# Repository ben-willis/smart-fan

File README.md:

# Smart Fan Project

A WiFi-enabled smart fan controller built on ESP32-S3 with Home Assistant integration, using ESPHome for firmware management.

## Overview

This project transforms a traditional fan into a smart, connected device with the following capabilities:
- **WiFi Connectivity**: ESP32-S3 microcontroller for wireless control
- **Home Assistant Integration**: Full API integration for home automation
- **Physical Controls**: GPIO-based buttons for manual operation
- **IR Remote Support**: NEC protocol infrared remote control
- **Advanced Features**: 3-speed control, oscillation mode, preset modes (Sleep, Nature, Normal)
- **Custom PCB**: Professionally designed KiCad PCB with production-ready Gerber files

## Documentation

- [Docs Index](docs/README.md)
- [Project Story](docs/project-story.md)
- [UART Protocol](docs/uart-protocol.md)
- [Hardware Notes](docs/hardware-notes.md)

If you are new to this repository, start with [Project Story](docs/project-story.md), then use [UART Protocol](docs/uart-protocol.md) while reviewing firmware behavior.

## Hardware

### Microcontroller
- **Board**: ESP32-S3-DevKitC-1
- **Framework**: Arduino

### Physical Controls
- **On/Off Button**: GPIO11
- **Speed Control Button**: GPIO10 (cycles through 3 speeds)
- **Oscillation Toggle Button**: GPIO34
- **Mode Button**: GPIO9 (reserved for future use)
- **Timer Button**: GPIO8 (reserved for future use)

### IR Remote
- **Protocol**: NEC
- **Address**: 0xFE01
- **Supported Commands**:
  - On/Off: 0xFC03
  - Speed Cycle: 0xF807
  - Oscillation: 0xEC13

### Visual Indicators
- **Low Speed LED**: GPIO15
- **Medium Speed LED**: GPIO18
- **High Speed LED**: GPIO19
- **Normal Mode LED**: GPIO14
- **Rhythm Mode LED**: GPIO17
- **Sleep Mode LED**: GPIO20

### Communication
- **Fan UART**: GPIO43 (TX), GPIO44 (RX) @ 334 baud
- **Remote Receiver**: GPIO7 (inverted, NEC protocol via RMT channel 4)

## Features

### Fan Control
- **3-Speed Operation**: Low, Medium, High
- **Oscillation Mode**: On/Off toggle
- **Preset Modes**: 
  - Sleep mode
  - Nature mode
  - Normal mode
- **State Preservation**: Always powers off on restart

### Connectivity
- **WiFi**: Configurable SSID and password with fallback hotspot
- **API**: Home Assistant encrypted API communication
- **OTA Updates**: Over-the-air firmware updates via ESPHome

### Debugging
- **Serial Logging**: DEBUG level logging enabled
- **UART Debug**: Bidirectional UART debugging for fan communication
- **State Tracking**: Comprehensive logging of all state changes

## Project Structure

```
smart-fan/
├── README.md                  # Project documentation
├── secrets.yaml               # WiFi and API credentials (not in git)
│
├── firmware/                  # ESPHome firmware configuration
│   └── smart-fan.yml          # Main ESPHome configuration
│
├── hardware/                  # KiCad PCB design files
│   ├── smart-fan.kicad_sch    # Schematic
│   ├── smart-fan.kicad_pcb    # PCB layout
│   ├── smart-fan.kicad_pro    # Project file
│   ├── Gerber/                # Manufacturing files
│   │   ├── smart-fan-F_Cu.gbr
│   │   ├── smart-fan-B_Cu.gbr
│   │   ├── smart-fan-*.gbr    # Additional layers
│   │   ├── smart-fan-PTH.drl
│   │   └── smart-fan-NPTH.drl
│   └── production/            # Production data
│       ├── bom.csv            # Bill of materials
│       ├── designators.csv
│       ├── positions.csv      # Pick & place
│       └── netlist.ipc
│
├── docs/                      # Project docs, protocol notes, and hardware references
│
└── venv/                      # Python virtual environment
```

## Setup & Installation

### Prerequisites
- Python 3.8+
- ESPHome CLI or Web UI
- ESP32-S3-DevKitC-1 board
- USB-C cable for programming

### Configuration

1. **Create secrets.yaml** with the following variables:
   ```yaml
   api_encryption_key: "your_api_key_here"
   ota_password: "your_ota_password"
   wifi_ssid: "your_wifi_ssid"
   wifi_password: "your_wifi_password"
   ap_password: "fallback_hotspot_password"
   ```

2. **Create a virtual environment and install dependencies**:
   ```bash
   python -m venv venv
   source venv/Scripts/activate
   python -m pip install -r requirements.txt
   ```

3. **Build and Upload Firmware**:
   ```bash
   esphome run firmware/smart-fan.yml
   ```

4. **First Flash**:
   - Connect ESP32-S3 via USB-C
   - Select the COM port
   - Let ESPHome handle the flashing process

### WiFi & API Setup

- **Normal Operation**: Connects to specified WiFi SSID
- **Fallback Mode**: If WiFi connection fails, opens "Smart Fan Fallback Hotspot"
- **API Encryption**: Uses Home Assistant encrypted API for secure communication
- **OTA Updates**: After initial flash, updates can be done wirelessly

## Home Assistant Integration

Once configured, the Smart Fan will appear in Home Assistant with:
- **Fan entity**: Full control (on/off, speed, oscillation)
- **Preset modes**: Select Sleep, Nature, or Normal modes
- **Binary sensors**: Button press detection
- **Switches**: Individual control for lights and modes

Add to Home Assistant `configuration.yaml`:
```yaml
esphome:
  - firmware/smart-fan.yml
```

## Development

### Building PCB
- KiCad 8.0+ compatible
- Design files in `hardware/`
- Gerber files ready for ordering from fabricators
- Production data includes BOM, designators, and pick & place positions

### Serial Communication
The fan communicates via UART at 334 baud. Commands are 5-byte packets with checksums:
- Format: `[0x5a, SPEED_BITS, MODE_BITS, OSCILLATION_BITS, CHECKSUM]`
- See `docs/uart-protocol.md` for protocol details

### OTA Updates
After initial programming, update firmware wirelessly:
```bash
esphome run firmware/smart-fan.yml
```

## Debugging

### View Logs
```bash
esphome logs firmware/smart-fan.yml
```

### Monitor UART Communication
UART debugging is enabled with bidirectional logging. Connect to the serial monitor to see raw commands sent to the fan:
```bash
esphome logs firmware/smart-fan.yml
```

## Future Enhancements

- Mode button functionality for additional control modes
- Timer button integration for scheduled operation
- Display integration for status information
- Additional preset modes and customization
- Mobile app control via Home Assistant

## License

[Specify your license here]

## References

- [ESPHome Documentation](https://esphome.io/)
- [Home Assistant](https://www.home-assistant.io/)
- [ESP32-S3 DevKitC-1](https://docs.espressif.com/projects/esp-idf/en/latest/esp32s3/hw-reference/esp32s3/user-guide-devkitc-1.html)
- [KiCad Documentation](https://docs.kicad.org/)

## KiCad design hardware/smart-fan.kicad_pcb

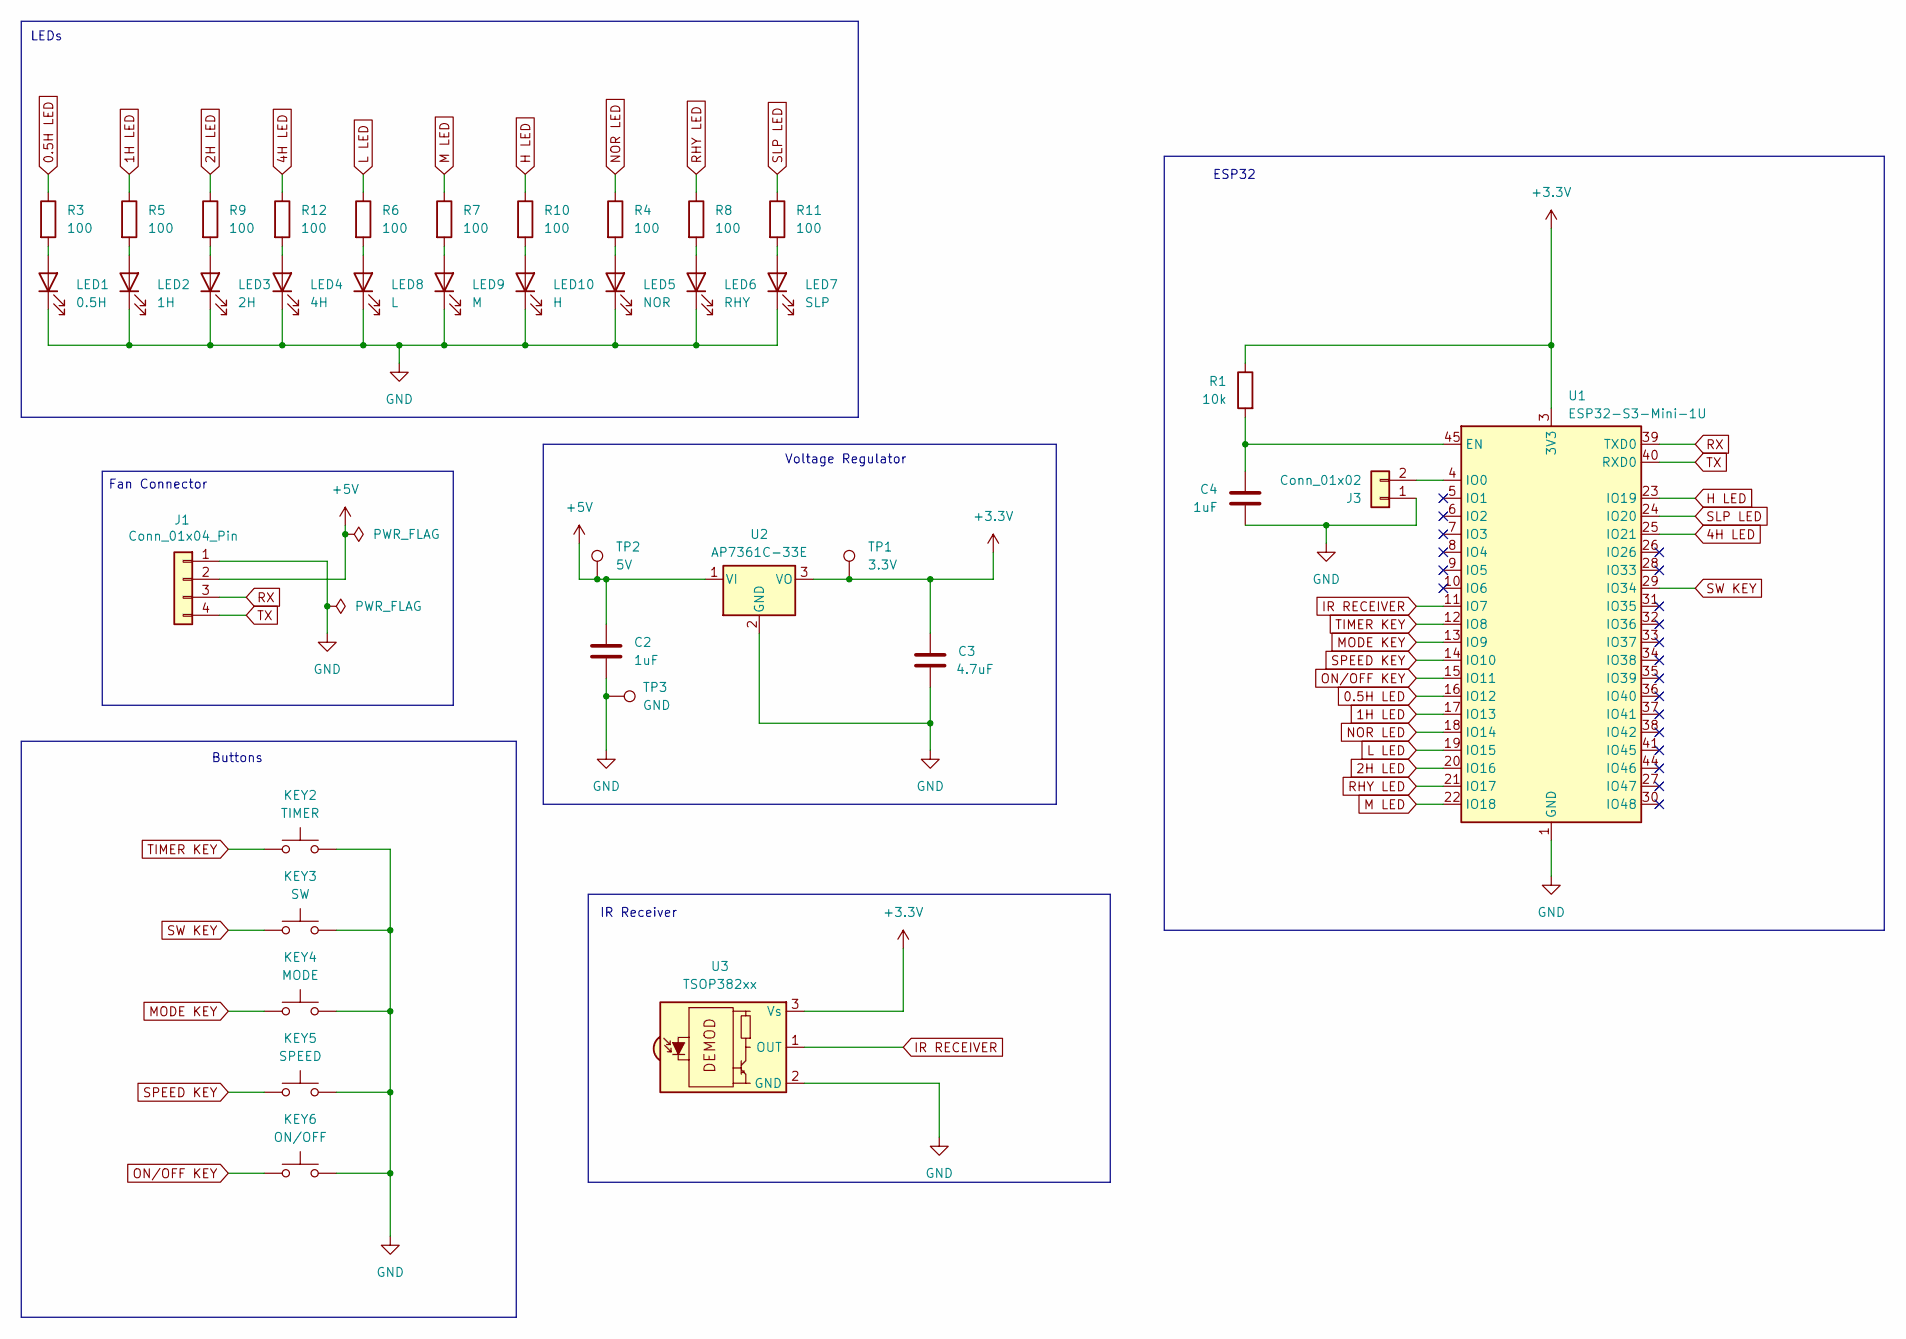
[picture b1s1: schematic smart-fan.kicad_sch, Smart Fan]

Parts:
C2: 1uF; C_1206_3216Metric; LCSC Part # C13585
C3: 4.7uF; C_1206_3216Metric; LCSC Part # C24497
C4: 1uF; C_1206_3216Metric; LCSC Part # C24497
J1: Conn_01x04_Pin; JST_XH_S4B-XH-A_1x04_P2.50mm_Horizontal; LCSC Part # C2286
J3: Conn_01x02; PinHeader_1x02_P2.54mm_Horizontal
KEY2: TIMER; SW_PUSH_6mm_H9.5mm; LCSC Part # C2837519
KEY3: SW; SW_PUSH_6mm_H9.5mm; LCSC Part # C2837519
KEY4: MODE; SW_PUSH_6mm_H9.5mm; LCSC Part # C2837519
KEY5: SPEED; SW_PUSH_6mm_H9.5mm; LCSC Part # C2837519
KEY6: ON/OFF; SW_PUSH_6mm_H9.5mm; LCSC Part # C2837519
LED1: 0.5H; LED_D3.0mm; LCSC Part # C330760
LED2: 1H; LED_D3.0mm; LCSC Part # C330760
LED3: 2H; LED_D3.0mm; LCSC Part # C330760
LED4: 4H; LED_D3.0mm; LCSC Part # C330760
LED5: NOR; LED_D3.0mm; LCSC Part # C330760
LED6: RHY; LED_D3.0mm; LCSC Part # C330760
LED7: SLP; LED_D3.0mm; LCSC Part # C330760
LED8: L; LED_D3.0mm; LCSC Part # C330760
LED9: M; LED_D3.0mm; LCSC Part # C330760
LED10: H; LED_D3.0mm; LCSC Part # C330760
R1: 10k; R_1206_3216Metric; LCSC Part # C25804
R3, R4, R5, R6, R7, R8, R9, R10, R11, R12: 100; R_1206_3216Metric; LCSC Part # C22859
TP1: 3.3V; TestPoint_Pad_D2.0mm
TP2: 5V; TestPoint_Pad_D2.0mm
TP3: GND; TestPoint_Pad_D2.0mm
U1: ESP32-S3-Mini-1U; ESP32-S2-MINI-1U; LCSC Part # C2980299
U2: AP7361C-33E; SOT-223-3_TabPin2; LCSC Part # C5250992
U3: TSOP382xx; Vishay_MINICAST-3Pin

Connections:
0.5H LED: R3.1, U1.16 (IO12)
1H LED: R5.1, U1.17 (IO13)
2H LED: R9.1, U1.20 (IO16)
4H LED: R12.1, U1.25 (IO21)
+3.3V: C3.1, R1.1, TP1.1, U1.3 (3V3), U2.3 (VO), U3.3 (Vs)
+5V: C2.1, J1.2, TP2.1, U2.1 (VI)
GND: C2.2, C3.2, C4.2, J1.1, J3.1, KEY2.2, KEY3.2, KEY4.2, KEY5.2, KEY6.2, LED1.1 (K), LED2.1 (K), LED3.1 (K), LED4.1 (K), LED5.1 (K), LED6.1 (K), LED7.1 (K), LED8.1 (K), LED9.1 (K), LED10.1 (K), TP3.1, U1.1 (GND), U1.2 (GND), U1.42 (GND), U1.43 (GND), U1.46 (GND), U1.47 (GND), U1.48 (GND), U1.49 (GND), U1.50 (GND), U1.51 (GND), U1.52 (GND), U1.53 (GND), U1.54 (GND), U1.55 (GND), U1.56 (GND), U1.57 (GND), U1.58 (GND), U1.59 (GND), U1.60 (GND), U1.61 (GND), U1.62 (GND), U1.63 (GND), U1.64 (GND), U1.65 (GND), U2.2 (GND), U3.2 (GND)
H LED: R10.1, U1.23 (IO19)
IR RECEIVER: U1.11 (IO7), U3.1 (OUT)
L LED: R6.1, U1.19 (IO15)
M LED: R7.1, U1.22 (IO18)
MODE KEY: KEY4.1, U1.13 (IO9)
NOR LED: R4.1, U1.18 (IO14)
unnamed: J3.2, U1.4 (IO0)
unnamed: LED1.2 (A), R3.2
unnamed: LED2.2 (A), R5.2
unnamed: LED3.2 (A), R9.2
unnamed: LED4.2 (A), R12.2
unnamed: LED5.2 (A), R4.2
unnamed: LED6.2 (A), R8.2
unnamed: LED7.2 (A), R11.2
unnamed: LED8.2 (A), R6.2
unnamed: LED9.2 (A), R7.2
unnamed: LED10.2 (A), R10.2
unnamed: C4.1, R1.2, U1.45 (EN)
ON/OFF KEY: KEY6.1, U1.15 (IO11)
RHY LED: R8.1, U1.21 (IO17)
RX: J1.3, U1.39 (TXD0)
SLP LED: R11.1, U1.24 (IO20)
SPEED KEY: KEY5.1, U1.14 (IO10)
SW KEY: KEY3.1, U1.29 (IO34)
TIMER KEY: KEY2.1, U1.12 (IO8)
TX: J1.4, U1.40 (RXD0)

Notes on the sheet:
Fan Connector
Buttons
IR Receiver
LEDs
ESP32
Voltage Regulator

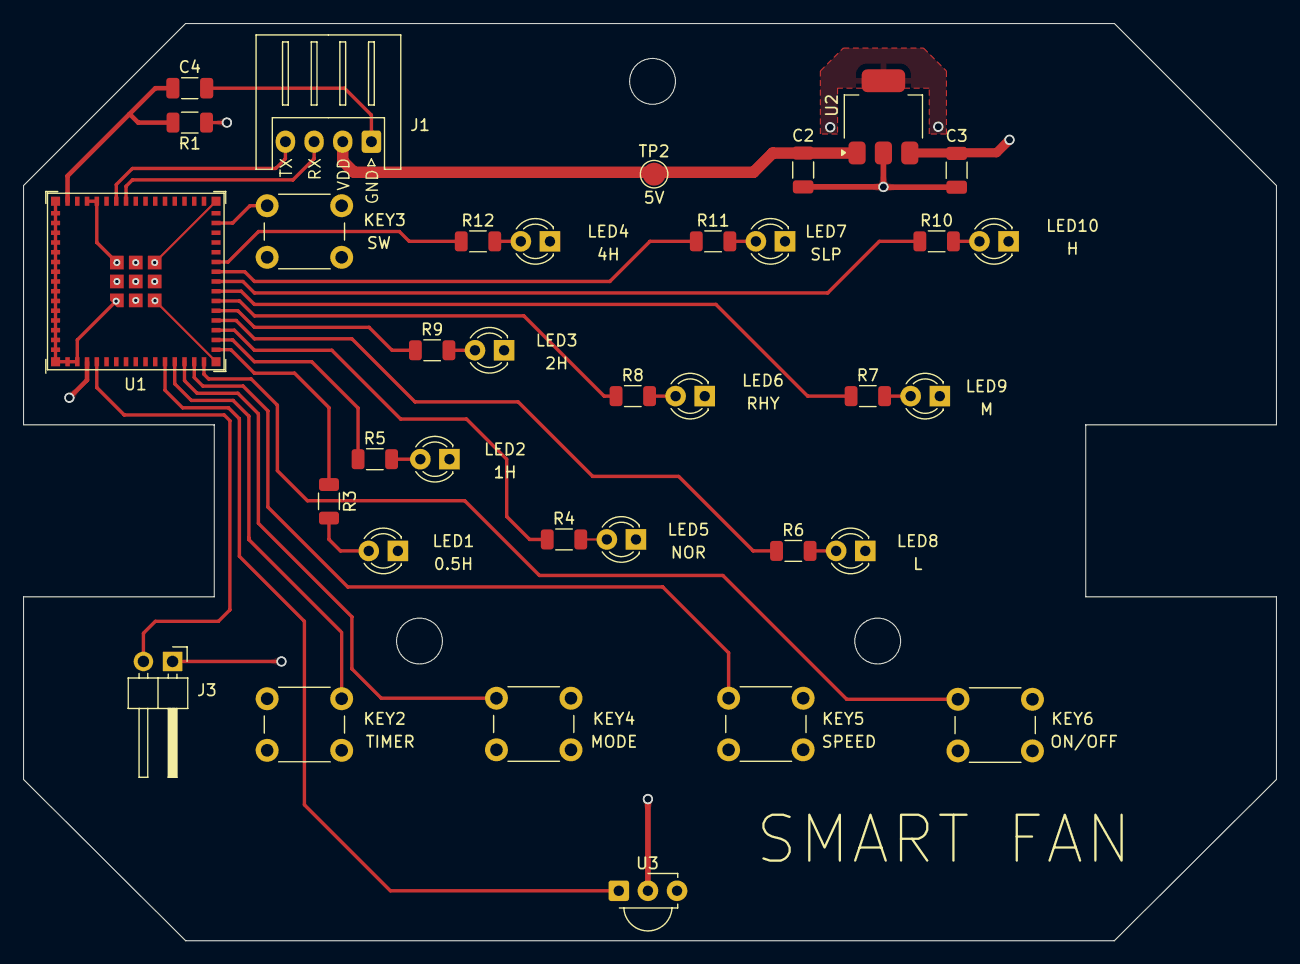
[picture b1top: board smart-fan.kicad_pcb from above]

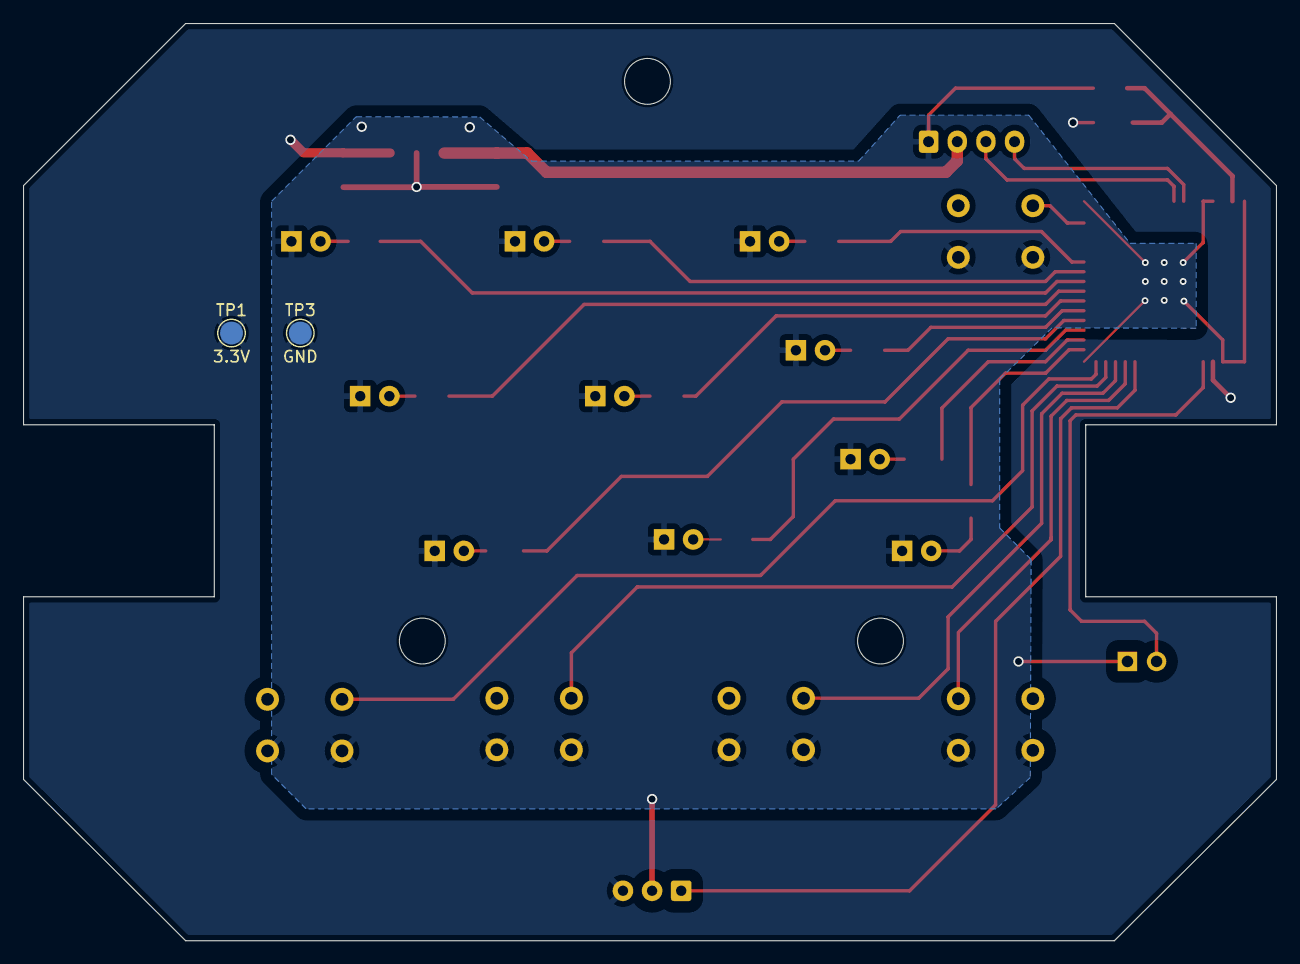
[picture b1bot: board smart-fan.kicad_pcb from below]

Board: 2 copper layers, 109.3 x 80.0 mm, 37 parts (2 on the bottom side), 33 nets.

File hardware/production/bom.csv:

Designator,Footprint,Quantity,Value,LCSC Part #
C2,1206,1,1uF,C1848
C3,1206,1,4.7uF,C51205
C4,1206,1,1uF,C1848
J1,JST_XH_S4B-XH-A_1x04_P2.50mm_Horizontal,1,Conn_01x04_Pin,C157925
J3,PinHeader_1x02_P2.54mm_Horizontal,1,Conn_01x02,C492410
KEY2,SW_PUSH_6mm_H9.5mm,1,TIMER,C455119
KEY3,SW_PUSH_6mm_H9.5mm,1,SW,C455119
KEY4,SW_PUSH_6mm_H9.5mm,1,MODE,C455119
KEY5,SW_PUSH_6mm_H9.5mm,1,SPEED,C455119
KEY6,SW_PUSH_6mm_H9.5mm,1,ON/OFF,C455119
LED1,LED_D3.0mm,1,Blue,C330760
LED10,LED_D3.0mm,1,Blue,C330760
LED2,LED_D3.0mm,1,Blue,C330760
LED3,LED_D3.0mm,1,Blue,C330760
LED4,LED_D3.0mm,1,Blue,C330760
LED5,LED_D3.0mm,1,Blue,C330760
LED6,LED_D3.0mm,1,Blue,C330760
LED7,LED_D3.0mm,1,Blue,C330760
LED8,LED_D3.0mm,1,Blue,C330760
LED9,LED_D3.0mm,1,Blue,C330760
R1,1206,1,10k,C17902
"R10, R11, R12, R3, R4, R5, R6, R7, R8, R9",1206,10,100,C17901
TP1,TestPoint_Pad_D2.0mm,1,3.3V,
TP2,TestPoint_Pad_D2.0mm,1,5V,
TP3,TestPoint_Pad_D2.0mm,1,GND,
U1,ESP32-S2-MINI-1U,1,ESP32-S3-Mini-1U,C2980299
U2,SOT-223-3_TabPin2,1,AP7361C-33E,C500795
U3,Vishay_MINICAST-3Pin,1,TSOP382xx,C141632

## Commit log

2026-05-09 Initial commit: Smart Fan ESP32 controller with ESPHome integration
    - Complete ESPHome firmware configuration with Home Assistant API
    - Custom KiCad PCB design with manufacturing outputs (Gerbers, BOM, positions, netlist)
    - Reverse-engineered UART protocol for fan control (334 baud, 5-byte frames)
    - Comprehensive project documentation covering teardown, protocol, and hardware design
    - GPIO mapping for buttons, LEDs, IR receiver, and fan UART communication
    - Production-ready files for PCB fabrication
2026-05-09 Add local timer control flow and HA timer sync
